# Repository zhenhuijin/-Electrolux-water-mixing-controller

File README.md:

# -Electrolux-water-mixing-controller
 伊莱克斯混水控制器 Electrolux water mixing controller

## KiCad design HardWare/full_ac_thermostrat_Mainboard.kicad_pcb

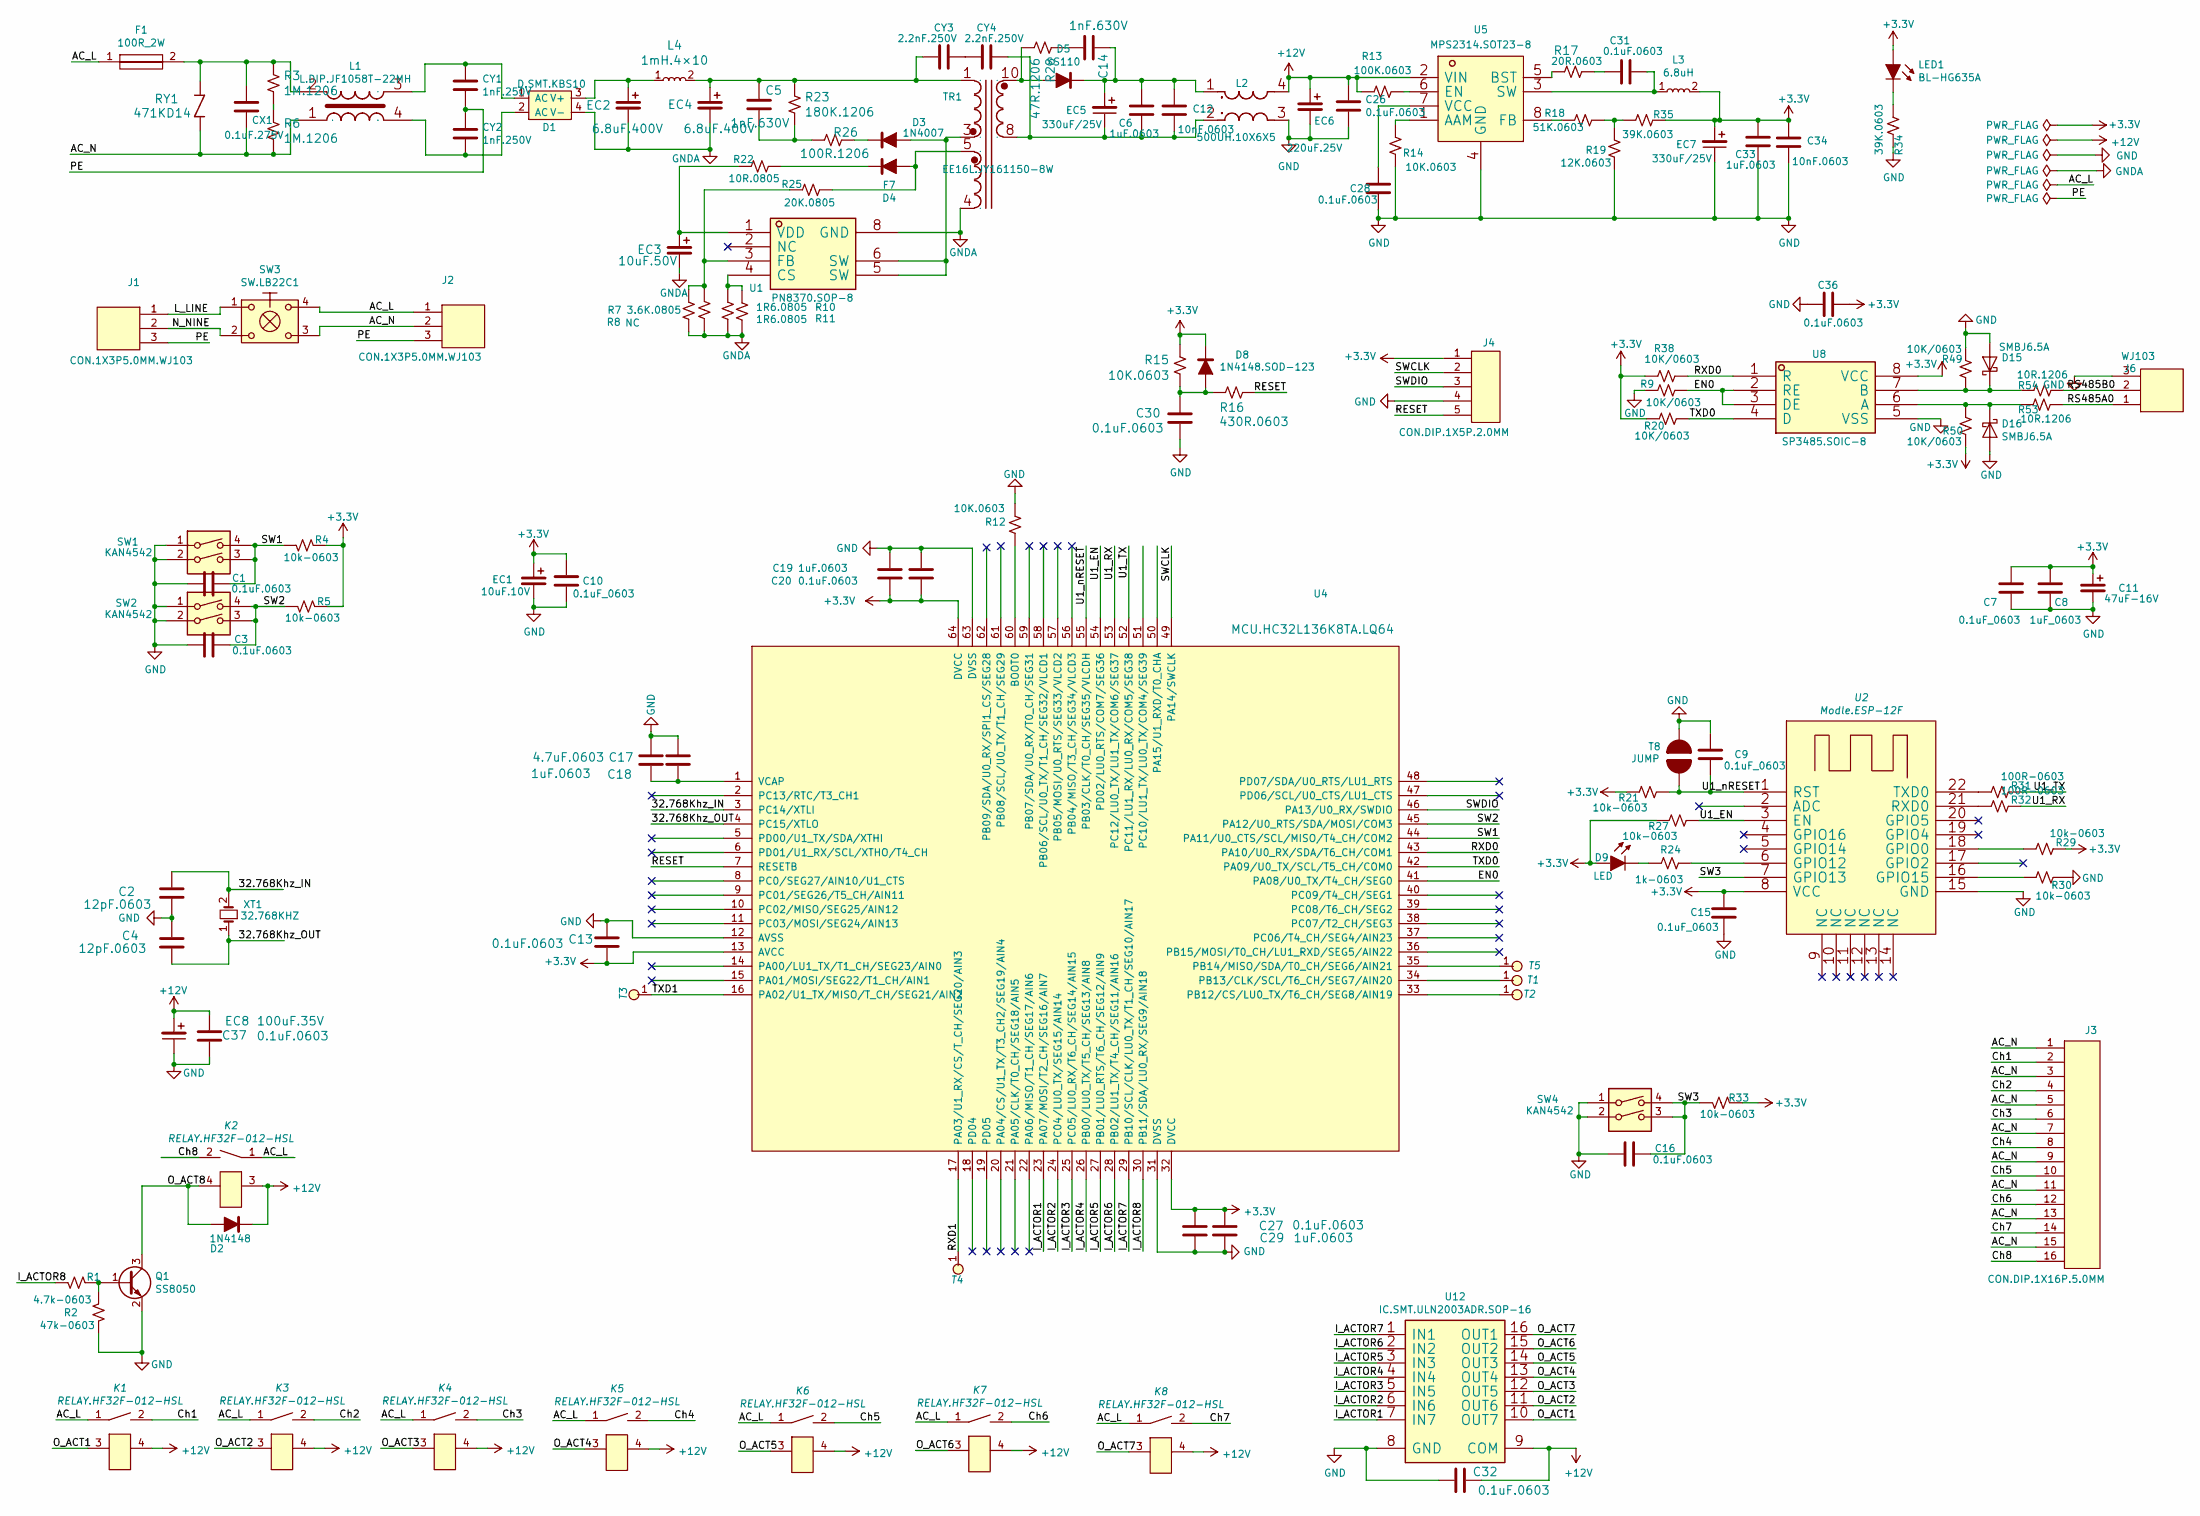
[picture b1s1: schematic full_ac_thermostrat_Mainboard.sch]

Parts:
C1, C3, C13, C16, C20, C26, C27, C28, C30, C31, C32, C36, C37: 0.1uF.0603; CAP.SMT.0603C
C2, C4: 12pF.0603; CAP.SMT.0603C
C5, C14: 1nF.630V; CAP.SMT.1206C
C6, C18, C19, C29, C33: 1uF.0603; CAP.SMT.0603C
C7, C9, C10, C15: 0.1uF_0603; CAP.SMT.0603C
C8: 1uF_0603; CAP.SMT.0603C
C11: 47uF-16V; CAP.SMT.47UF.16V
C12, C34: 10nF.0603; CAP.SMT.0603C
C17: 4.7uF.0603; CAP.SMT.0603C
CX1: 0.1uF.275V; CAP.DIP.X.0.1uF／275V
CY1, CY2: 1nF.250V; CAP.DIP.Y.102M／250V
CY3, CY4: 2.2nF.250V; CAP.DIP.Y.102M／250V
D1: D.SMT.KBS10; D.SMT.KBP310G
D2: 1N4148; D.SMT.1N4148.SOD-123
D3: 1N4007; D.SMT.1N4007.SOD-123
D4: F7; D.SMT.1N5819.SMA
D5: SS110; D.SMT.1N5819.SMA
D8: 1N4148.SOD-123; D.SMT.1N4148.SOD-123
D9: LED; D.LED.SMT.0805
D15, D16: SMBJ6.5A; D.SMT.SMBJ6.5A.D0-214
EC1: 10uF.10V; CAP.SMT.TAJA106M010RNJ
EC2, EC4: 6.8uF.400V; CAP.DIP.6.8UF.400V.10MM2
EC3: 10uF.50V; CAP.DIP.10uF／50V.5.2X11.6
EC5, EC7: 330uF/25V; CAP.SMT.220UF.16V
EC6: 220uF.25V; CAP.SMT.220UF.16V
EC8: 100uF.35V; CAP.SMT.220UF.16V
F1: 100R_2W; FUSE.3.15A
J1, J2: CON.1X3P5.0MM.WJ103; CON_DIP_1X3PIN_5.0MM_WJ103
J3: CON.DIP.1X16P.5.0MM; CON_DIP_1X16PIN_5.0MM_WJ103
J4: CON.DIP.1X5P.2.0MM; CON_DIP_1X5PIN_2.0MM
J6: WJ103; CON_DIP_1X3PIN_5.0MM_WJ103
K1, K2, K3, K4, K5, K6, K7, K8: RELAY.HF32F-012-HSL
L1: L.DIP.JF1058T-22MH; L.DIP.JF1058T-3.5MH
L2: 500UH.10X6X5; L.DIP.500UH.10X6X5
L3: 6.8uH; L.SMT.3012S
L4: 1mH.4×10; L.PID.2.2mH
LED1: BL-HG635A; D.BL-HG635A-TRB-LED
Q1: SS8050; BJT.SMT.SOT-23
R1: 4.7k-0603; RES.SMT.0603
R2: 47k-0603; RES.SMT.0603
R3, R6: 1M.1206; RES.SMT.1210
R4, R5, R21, R27, R29, R30, R33: 10k-0603; RES.SMT.0603
R7: 3.6K.0805; RES.SMT.0805
R8: NC; RES.SMT.0805
R9, R20, R38, R49, R50: 10K/0603; RES.SMT.0603
R10, R11: 1R6.0805; RES.SMT.0805
R12, R14, R15: 10K.0603; RES.SMT.0603
R13: 100K.0603; RES.SMT.0603
R16: 430R.0603; RES.SMT.0603
R17: 20R.0603; RES.SMT.0603
R18: 51K.0603; RES.SMT.0603
R19: 12K.0603; RES.SMT.0603
R22: 10R.0805; RES.SMT.0805
R23: 180K.1206; RES.SMT.1210
R24: 1k-0603; RES.SMT.0603
R25: 20K.0805; RES.SMT.0805
R26: 100R.1206; RES.SMT.1210
R28: 47R.1206; RES.SMT.1210
R31, R32: 100R-0603; RES.SMT.0603
R34, R35: 39K.0603; RES.SMT.0603
R53, R54: 10R.1206; RES.SMT.1210
RY1: 471KD14; RES.DIP.RV.TDK471KD14
SW1, SW2, SW4: KAN4542; SWITCH_KAN4542
SW3: SW.LB22C1; SWITCH_LB22C1
T1, T2, T3, T4, T5: TSET; OTHER.TEST
T8: JUMP; OTHER.JUMP
TR1: EE16L.JY161150-8W; L.DIP.TRANS.EE16L-5W
U1: PN8370.SOP-8; IC.SMT.SOIC-8
U2: Modle.ESP-12F
U4: MCU.HC32L136K8TA.LQ64; MCU.LQFP.64.7x7mm.0.4mm
U5: MPS2314.SOT23-8; IC.SMT.SOT23-8
U8: SP3485.SOIC-8; SOIC-8
U12: IC.SMT.ULN2003ADR.SOP-16; SOIC-16
XT1: 32.768KHZ; OSC.SMT.32.768KHz

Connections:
+3V3: C7.1, C8.1, C10.1, C11.1, C13.2, C15.1, C19.2, C20.2, C27.1, C29.1, C33.1, C34.1, C36.1, D8.1 (K), D9.2 (A), EC1.1, EC7.1, J4.1, L3.2, LED1.2 (A), R4.2, R5.2, R15.1, R20.2, R21.2, R27.2, R29.1, R33.2, R35.1, R38.2, R50.2, U2.8 (VCC), U4.13 (AVCC), U4.32 (DVCC), U4.64 (DVCC), U8.8 (VCC)
+12V: C26.1, C32.1, C37.1, D2.1 (K), EC6.1, EC8.1, K1.4, K2.3, K3.4, K4.4, K5.4, K6.4, K7.4, K8.4, L2.4, R13.1, U5.2 (VIN), U12.9 (COM)
/32.768Khz_IN: C2.1, U4.3 (PC14/XTLI), XT1.2
/32.768Khz_OUT: C4.2, U4.4 (PC15/XTLO), XT1.1
/AC_L: F1.1, J2.1, K1.1, K2.1, K3.1, K4.1, K5.1, K6.1, K7.1, K8.1, SW3.4
/AC_N: CX1.2, J2.2, J3.1, J3.3, J3.5, J3.7, J3.9, J3.11, J3.13, J3.15, L1.1, R6.2, RY1.2, SW3.3
/Ch1: J3.2, K1.2
/Ch2: J3.4, K3.2
/Ch3: J3.6, K4.2
/Ch4: J3.8, K5.2
/Ch5: J3.10, K6.2
/Ch6: J3.12, K7.2
/Ch7: J3.14, K8.2
/Ch8: J3.16, K2.2
/EN0: R9.1, U4.41 (PA08/U0_TX/T4_CH/SEG0), U8.2 (RE), U8.3 (DE)
/I_ACTOR1: U4.23 (PA07/MOSI/T2_CH/SEG16/AIN7), U12.7 (IN7)
/I_ACTOR2: U4.24 (PC04/LU0_TX/SEG15/AIN14), U12.6 (IN6)
/I_ACTOR3: U4.25 (PC05/LU0_RX/T6_CH/SEG14/AIN15), U12.5 (IN5)
/I_ACTOR4: U4.26 (PB00/LU0_TX/T5_CH/SEG13/AIN8), U12.4 (IN4)
/I_ACTOR5: U4.27 (PB01/LU0_RTS/T6_CH/SEG12/AIN9), U12.3 (IN3)
/I_ACTOR6: U4.28 (PB02/LU1_TX/T4_CH/SEG11/AIN16), U12.2 (IN2)
/I_ACTOR7: U4.29 (PB10/SCL/CLK/LU0_TX/T1_CH/SEG10/AIN17), U12.1 (IN1)
/I_ACTOR8: R1.1, U4.30 (PB11/SDA/LU0_RX/SEG9/AIN18)
/L_LINE: J1.1, SW3.1
/N_NINE: J1.2, SW3.2
/O_ACT1: K1.3, U12.10 (OUT7)
/O_ACT2: K3.3, U12.11 (OUT6)
/O_ACT3: K4.3, U12.12 (OUT5)
/O_ACT4: K5.3, U12.13 (OUT4)
/O_ACT5: K6.3, U12.14 (OUT3)
/O_ACT6: K7.3, U12.15 (OUT2)
/O_ACT7: K8.3, U12.16 (OUT1)
/O_ACT8: D2.2 (A), K2.4, Q1.3
/PE: CY1.2, CY2.1, J1.3, J2.3
/RESET: J4.5, R16.2, U4.7 (RESETB)
/RS485A0: J6.1, R53.2
/RS485B0: J6.2, R54.2
/RXD0: R38.1, U4.43 (PA10/U0_RX/SDA/T6_CH/COM1), U8.1 (R)
/RXD1: T4.1, U4.17 (PA03/U1_RX/CS/T_CH/SEG20/AIN3)
/SW1: C1.1, R4.1, SW1.3, SW1.4, U4.44 (PA11/U0_CTS/SCL/MISO/T4_CH/COM2)
/SW2: C3.1, R5.1, SW2.3, SW2.4, U4.45 (PA12/U0_RTS/SDA/MOSI/COM3)
/SW3: C16.1, R33.1, SW4.3, SW4.4, U2.7 (GPIO13)
/SWCLK: J4.2, U4.49 (PA14/SWCLK)
/SWDIO: J4.3, U4.46 (PA13/U0_RX/SWDIO)
/TXD0: R20.1, U4.42 (PA09/U0_TX/SCL/T5_CH/COM0), U8.4 (D)
/TXD1: T3.1, U4.16 (PA02/U1_TX/MISO/T_CH/SEG21/AIN2)
/U1_EN: R27.1, U2.3 (EN), U4.54 (PD02/LU0_RTS/COM7/SEG36)
/U1_RX: R32.1, U4.53 (PC12/LU0_TX/LU1_TX/COM6/SEG37)
/U1_TX: R31.1, U4.52 (PC11/LU1_RX/LU0_RX/COM5/SEG38)
/U1_nRESET: C9.2, R21.1, T8.2, U2.1 (RST), U4.55 (PB03/CLK/T0_CH/SEG35/VLCDH)
GND: C1.2, C2.2, C3.2, C4.1, C7.2, C8.2, C9.1, C10.2, C11.2, C13.1, C15.2, C16.2, C17.2, C18.2, C19.1, C20.1, C26.2, C27.2, C28.2, C29.2, C30.2, C32.2, C33.2, C34.2, C36.2, C37.2, D15.2 (A), D16.2 (A), EC1.2, EC6.2, EC7.2, EC8.2, J4.4, J6.3, L2.3, Q1.2, R2.2, R9.2, R12.1, R14.1, R19.2, R30.1, R34.1, R49.1, SW1.1, SW1.2, SW2.1, SW2.2, SW4.1, SW4.2, T8.1, U2.15 (GND), U4.12 (AVSS), U4.31 (DVSS), U4.63 (DVSS), U5.4 (GND), U8.5 (VSS), U12.8 (GND)
GNDA: D1.4 (V-), EC2.2, EC3.2, EC4.2, R7.2, R8.2, R10.2, R11.2, TR1.4, U1.8 (GND)
unnamed: C5.1, CY3.2, EC4.1, L4.2, R23.1, TR1.1
unnamed: C5.2, R23.2, R26.2
unnamed: C6.1, C12.1, C14.1, D5.1 (K), EC5.1, L2.1
unnamed: C6.2, C12.2, CY4.1, EC5.2, L2.2, TR1.8
unnamed: C14.2, R28.1
unnamed: C17.1, C18.1, U4.1 (VCAP)
unnamed: C28.1, U5.7 (VCC)
unnamed: C30.1, D8.2 (A), R15.2, R16.1
unnamed: C31.1, R17.1
unnamed: C31.2, L3.1, U5.3 (SW)
unnamed: CX1.1, F1.2, L1.2, R3.1, RY1.1
unnamed: CY1.1, D1.1 (AC), L1.3
unnamed: CY2.2, D1.2 (AC), L1.4
unnamed: CY3.1, CY4.2
unnamed: D1.3 (V+), EC2.1, L4.1
unnamed: D3.1 (K), R26.1
unnamed: D3.2 (A), TR1.3, U1.5 (SW), U1.6 (SW)
unnamed: D4.1 (K), R22.2
unnamed: D4.2 (A), R25.2, TR1.5
unnamed: D5.2 (A), R28.2, TR1.10
unnamed: D9.1 (K), R24.1
unnamed: D15.1 (K), R49.2, R54.1, U8.7 (B)
unnamed: D16.1 (K), R50.1, R53.1, U8.6 (A)
unnamed: EC3.1, R22.1, U1.1 (VDD)
unnamed: LED1.1 (K), R34.2
unnamed: Q1.1, R1.2, R2.1
unnamed: R3.2, R6.1
unnamed: R10.1, R11.1, U1.4 (CS)
unnamed: R12.2, U4.60 (BOOT0)
unnamed: R13.2, U5.6 (EN)
unnamed: R14.2, U5.1 (AAM)
unnamed: R17.2, U5.5 (BST)
unnamed: R18.1, R19.1, R35.2
unnamed: R18.2, U5.8 (FB)
unnamed: R24.2, U2.6 (GPIO12)
unnamed: R7.1, R8.1, R25.1, U1.3 (FB)
unnamed: R29.2, U2.18 (GPIO0)
unnamed: R30.2, U2.16 (GPIO15)
unnamed: R31.2, U2.22 (TXD0)
unnamed: R32.2, U2.21 (RXD0)
unnamed: T1.1, U4.34 (PB13/CLK/SCL/T6_CH/SEG7/AIN20)
unnamed: T2.1, U4.33 (PB12/CS/LU0_TX/T6_CH/SEG8/AIN19)
unnamed: T5.1, U4.35 (PB14/MISO/SDA/T0_CH/SEG6/AIN21)

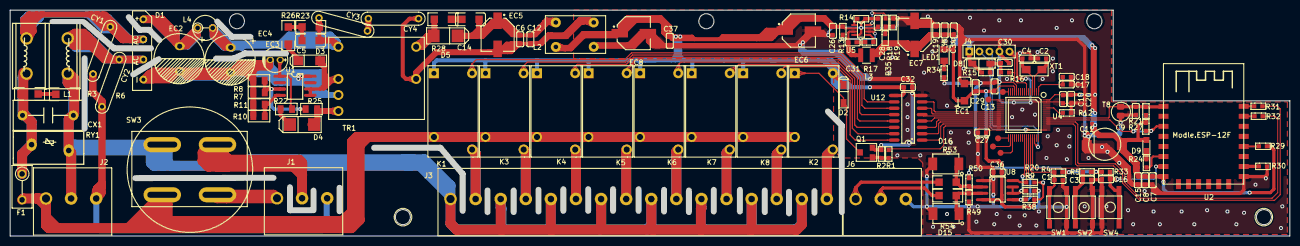
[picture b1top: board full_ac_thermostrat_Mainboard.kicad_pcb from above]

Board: 2 copper layers, 253.8 x 43.9 mm, 132 parts (0 on the bottom side), 95 nets.

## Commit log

2020-12-02 上传资料
2021-01-29 修改WiFi模块 安信可
